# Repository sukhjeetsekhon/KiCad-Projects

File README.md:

# KiCad-Projects
A repository of KiCad projects, PCBs, and modules that I make for fun or utility.

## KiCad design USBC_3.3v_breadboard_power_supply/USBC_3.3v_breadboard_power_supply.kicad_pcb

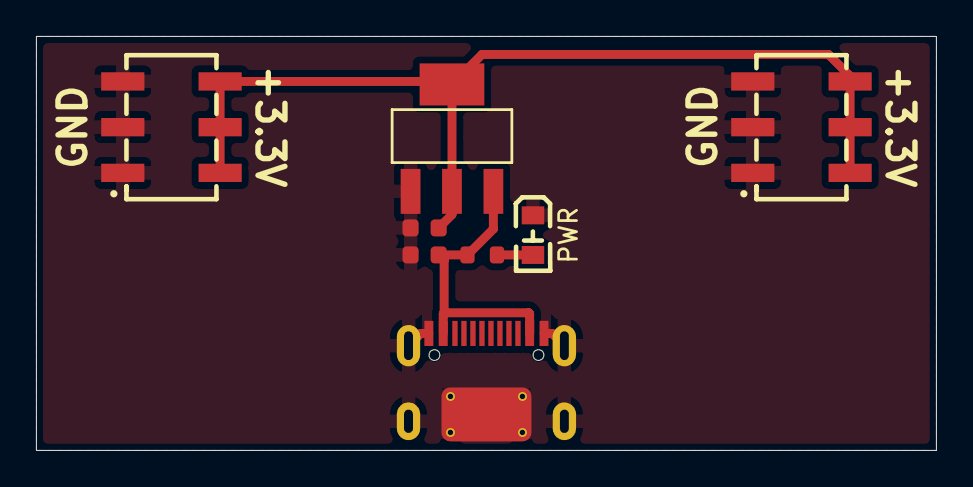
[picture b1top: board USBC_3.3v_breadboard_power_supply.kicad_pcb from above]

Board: 2 copper layers, 50.0 x 23.0 mm, 8 parts (0 on the bottom side), 4 nets.

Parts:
C1, C2: 22uF; C_0603
CN1, CN2: PM254-2-03-S-8_5
J1: Connector, USB-TYPE-C-16P; TYPE-C-SMD_HX-TYPE-C-16PIN
PWR: Red; FC-2012HRK-620D
R1: 2k; R_0603
U1: AMS1117-3_3

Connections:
5V: C2.2, J1.A9B4 (VBUS), J1.B9A4 (VBUS), R1.1, U1.3 (VIN)
+3.3V: C1.2, CN1.4, CN1.5, CN1.6, CN2.4, CN2.5, CN2.6, U1.2 (VOUT), U1.4 (VOUT)
GND: C1.1, C2.1, CN1.1, CN1.2, CN1.3, CN2.1, CN2.2, CN2.3, J1.A12B1 (GND), J1.B12A1 (GND), J1.S1 (SHIELD), PWR.1 (-), U1.1 (GND)
unnamed: PWR.2 (+), R1.2

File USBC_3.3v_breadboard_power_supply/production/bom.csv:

Designator,Footprint,Quantity,Value,LCSC Part #
"C1, C2",C_0603,2,22uF,C59461
"CN1, CN2",PM254-2-03-S-8_5,2,PM254-2-03-S-8_5,C3975148
J1,TYPE-C-SMD_HX-TYPE-C-16PIN,1,"Connector, USB-TYPE-C-16P",C2927039
PWR,FC-2012HRK-620D,1,Red,C84256
R1,R_0603,1,2k,C22975
U1,AMS1117-3_3,1,AMS1117-3_3,C6186

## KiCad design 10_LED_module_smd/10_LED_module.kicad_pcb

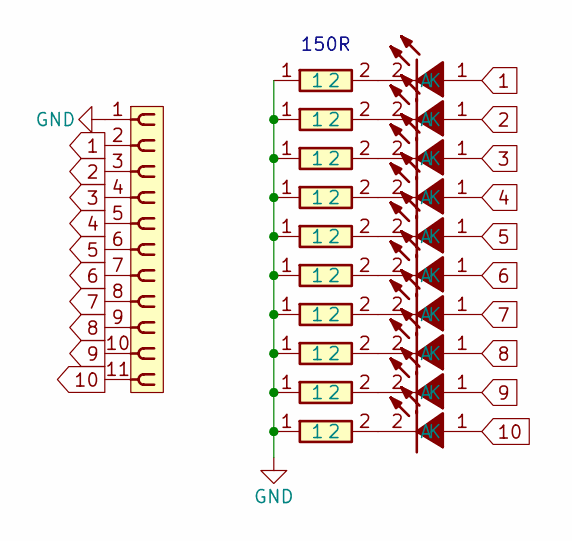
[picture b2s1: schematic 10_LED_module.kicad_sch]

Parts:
J1: PINHD_1x11_Female; PinSocket_1x11_P2.54mm_Vertical
LED1, LED2, LED3, LED4, LED5, LED6, LED7, LED8, LED9, LED10: KT-0603R; LED-SMD_4P-L1.6-W1.5_XL-1615RGBC-WS2812B; Manufacturer Part KT-0603R; LCSC C2286
R1, R2, R3, R4, R5, R6, R7, R8, R9, R10: 0603WAF1500T5E; R_0603; Manufacturer Part 0603WAF1500T5E; LCSC C22808

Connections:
1: J1.2, LED1.1 (A)
2: J1.3, LED2.1 (A)
3: J1.4, LED3.1 (A)
4: J1.5, LED4.1 (A)
5: J1.6, LED5.1 (A)
6: J1.7, LED6.1 (A)
7: J1.8, LED7.1 (A)
8: J1.9, LED8.1 (A)
9: J1.10, LED9.1 (A)
10: J1.11, LED10.1 (A)
GND: J1.1, R1.1, R2.1, R3.1, R4.1, R5.1, R6.1, R7.1, R8.1, R9.1, R10.1
unnamed: LED1.2 (K), R1.2
unnamed: LED2.2 (K), R2.2
unnamed: LED3.2 (K), R3.2
unnamed: LED4.2 (K), R4.2
unnamed: LED5.2 (K), R5.2
unnamed: LED6.2 (K), R6.2
unnamed: LED7.2 (K), R7.2
unnamed: LED8.2 (K), R8.2
unnamed: LED9.2 (K), R9.2
unnamed: LED10.2 (K), R10.2

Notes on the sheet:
150R

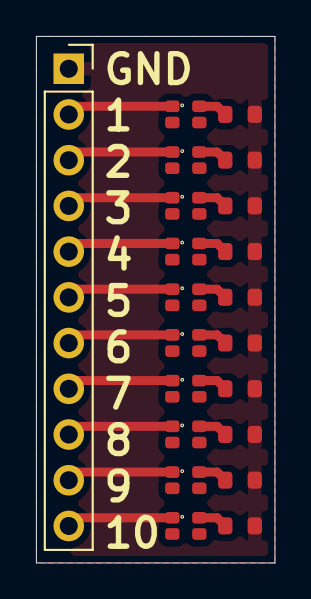
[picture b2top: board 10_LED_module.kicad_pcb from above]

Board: 2 copper layers, 13.2 x 29.2 mm, 21 parts (0 on the bottom side), 21 nets.

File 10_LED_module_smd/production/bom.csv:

Designator,Footprint,Quantity,Value,LCSC Part #
J1,PinSocket_1x11_P2.54mm_Vertical,1,PINHD_1x11_Female,
"LED1, LED10, LED2, LED3, LED4, LED5, LED6, LED7, LED8, LED9",LED-SMD_4P-L1.6-W1.5_XL-1615RGBC-WS2812B,10,KT-0603R,C2286
"R1, R10, R2, R3, R4, R5, R6, R7, R8, R9",R_0603,10,0603WAF1500T5E,C22808

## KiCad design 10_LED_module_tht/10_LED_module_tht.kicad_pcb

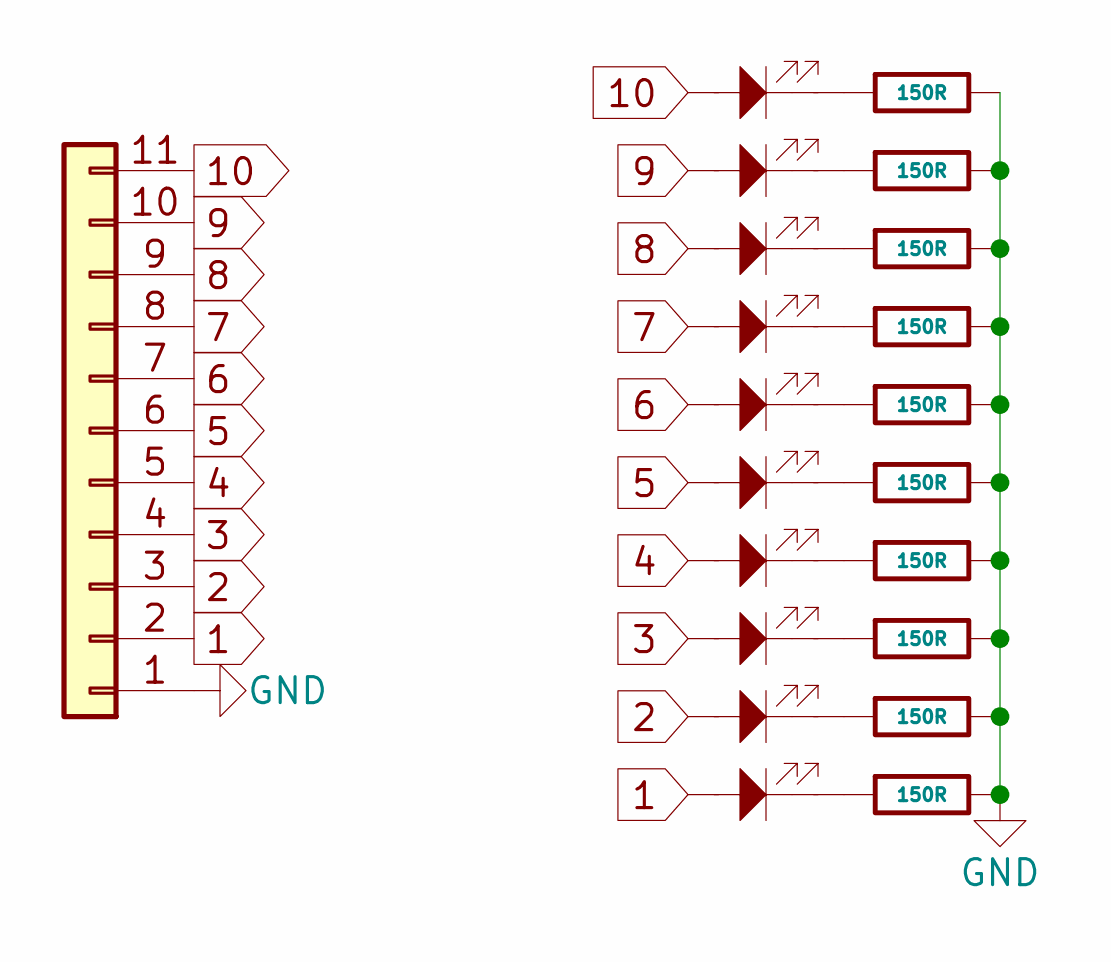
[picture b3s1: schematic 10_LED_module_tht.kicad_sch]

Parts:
D1, D2, D3, D4, D5, D6, D7, D8, D9, D10: LED; LED_D5.0mm
J1: Conn_01x11; 1x11_P2.54mm
R1, R2, R3, R4, R5, R6, R7, R8, R9, R10: 150R; R_Axial_DIN0207_L6.3mm_D2.5mm_P10.16mm_Horizontal

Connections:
1: D10.2, J1.2
2: D9.2, J1.3
3: D8.2, J1.4
4: D7.2, J1.5
5: D6.2, J1.6
6: D5.2, J1.7
7: D4.2, J1.8
8: D3.2, J1.9
9: D2.2, J1.10
10: D1.2, J1.11
GND: J1.1, R1.2, R2.2, R3.2, R4.2, R5.2, R6.2, R7.2, R8.2, R9.2, R10.2
unnamed: D1.1, R1.1
unnamed: D2.1, R2.1
unnamed: D3.1, R3.1
unnamed: D4.1, R4.1
unnamed: D5.1, R5.1
unnamed: D6.1, R6.1
unnamed: D7.1, R7.1
unnamed: D8.1, R8.1
unnamed: D9.1, R9.1
unnamed: D10.1, R10.1

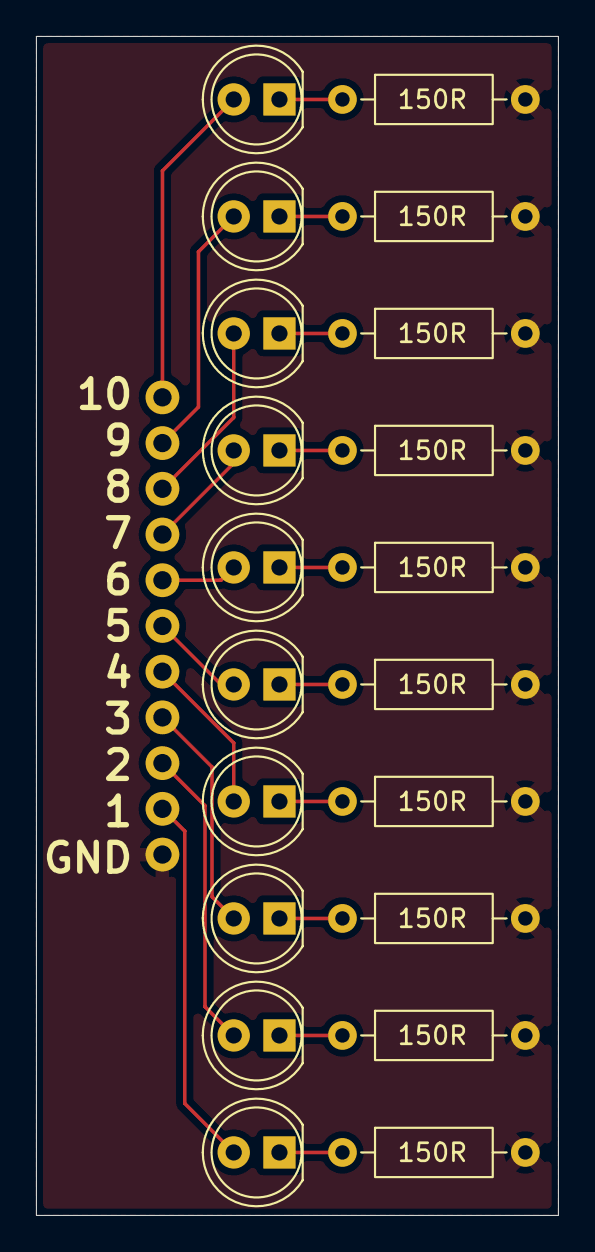
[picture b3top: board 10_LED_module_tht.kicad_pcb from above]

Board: 2 copper layers, 29.0 x 65.5 mm, 21 parts (0 on the bottom side), 21 nets.

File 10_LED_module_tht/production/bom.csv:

Designator,Footprint,Quantity,Value,LCSC Part #
"D1, D10, D2, D3, D4, D5, D6, D7, D8, D9",LED_D5.0mm,10,LED,
J1,1x11_P2.54mm,1,Conn_01x11,
"R1, R10, R2, R3, R4, R5, R6, R7, R8, R9",R_Axial_DIN0207_L6.3mm_D2.5mm_P10.16mm_Horizontal,10,150R,
